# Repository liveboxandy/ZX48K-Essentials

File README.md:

# ZX Spectrum 48K Essentials

This clone of the original (https://github.com/tomekszafranski/ZX48K-Essentials) has the following additions,

Full KiCAD 10 project including Schematic, PCB Data, Footprints, 3D Models and Symbols. 

No changes were made to the pcb layout or traces.

Symbols were adjusted to follow the original pdf schematic.
Footprints were adjusted to fit the original pcb layout. 
Vias were a best guess for sizes.
The BOM has not changed other than the JST connector should be JST_SHL_SM08B-SHLS-TF_1x08-1MP type.

Original README.md follows,

## Introduction

Sinclair ZX Spectrum 48K computer released in April 1982 was not the best one compared to its competitors but for sure became one of the most influential ones. A lot of hobbyists who nowadays collect, repair or mod Spectrum, might be tempted to create their own version - keeping the original idea/design that makes a Z80 system the Spectrum: ULA with its contended memory architecture, content of the ROM, original case and rubber keyboard but getting rid of all nonsenses where you could easily do better, even back then. 

It has to be said that this is not by any means revolutionary work. There are lots of similar projects and this one could easily be called Another Spectrum Clone but as mentioned before, every Spectrum lover would like to have his/her own version. I hope you like mine.

## Design

The idea is to leave all ZX Spectrum 48K components as they were and introduce only minimal changes. 

The main design decision concerns ULA. You might want to use original chip but it is difficult to get and you need to clone extensive analog video circuit (that occupies one third of the board) still getting relatively poor composite picture. On the other hand, you could use modern FPGA replacement that has RGB output - but this would not be ULA architecture (on the outside) any longer. I decided to use [vLA82S+](https://www.vretrodesign.com/products/vla82s-spectrum-ula-replacement-with-rgb-interface-and-ay-emulator-without-interface) by vRetro Design which is FPGA based ULA with RGB output but also a drop-in replacement for original chip so Sinclair's architecture will be preserved. Other changes are:

* Dynamically refreshed Lower RAM based on 4116 chips is replaced with more convenient static RAM which also allows to get rid of almost all of power supply section as -5V and +12V voltages are no longer needed. This is the solution commonly used in modern [memory replacements modules](https://www.retroleum.co.uk/spectrum-repairs-mods) – using set of flip-flops (74LS574) to hook up single RAM chip to raw/column address multiplexers used in original design.

* Dynamically refreshed Upper RAM 4132/64 chips use only one voltage, however they could easily be replaced with one 32KB static RAM chip. Memory type selection jumpers are no longer needed.
  
* While building your ZX Spectrum you probably will not source (difficult to get) original PROM but instead use modern EEPROM like W27C512 that you program with [content of the ROM](https://speccy4ever.speccy.org/_SIN.htm). ROM type jumpers are no longer needed.
  
* In power supply section efficient modern switching regulator is used that doesn't require a radiator. Also (as in MAX/Harlequin) bridge rectifier is added to save from mistakenly connecting power supply with wrong polarity (which from experience is likely to happen if you use more machines because Spectrum uses center-negative power jack while nowadays almost everything is center-positive).

Everything else is left intact.

## Parts

* Except for added components (marked with numbers 200+) all others <ins>have original references and are located in the same places</ins> on a PCB as in ZX Spectrum 48K Issue 3B. Four unmarked small elements are additional decoupling 100nF capacitors (P=2.5mm) for added ICs.
  
* Standard size 0,25W resistors are used, however compared to original their length is decreased from 0.6” to 0,5”. I really hate those banks of bus separation/pullup resistors so network ones are used wherever possible.
  
* Axial capacitors are used as in original design but you can install disc ones instead. I could not resist and left blue electrolytic capacitors (only two since there are no power and video sections), however there are mounting holes underneath (P=2.0mm) to use radial ones as well. 
  
* Original audio sockets are replaced with PJ-307 ones, commonly used in retro systems nowadays.
  
* Mini DIN8 connector (as in Harlequin 48K) is used to output RGB signal and mono sound to TV/monitor using [RGB Scart Lead cable](https://www.ebay.com/itm/253830448917?epid=17023035733&itmmeta=01JKTFD61QHFB48BB7ZDRB7SRS&hash=item3b19794715:g:KvwAAOSwlb5nn9B-).
  
* If you think using bridge rectifier is below you, shorten its pins: 1-4, 2-3 and don’t use it.

* Be aware that 40 ohm speaker might be difficult to find.

## Board

Here is KiCad project of the board.

Fully assembled ZX48essentials PCB, tested with [Diagnostic ROM](https://blog.retroleum.co.uk/electronics-articles/a-diagnostic-rom-image-for-the-zx-spectrum/), Kempston Pro Joystick Interface, [divMMC Future](https://www.tfw8b.com/product/divmmc-future-sinclair-zx-spectrum/), [ZX Interface 2](https://en.wikipedia.org/wiki/ZX_Interface_2) and [MaxDuino](https://lotharek.pl/productdetail.php?id=409).

## Remarks

* Because power section is severely reduced, only +5V is available on edge connector. Also no video signals are present.
  
* If you intend to put the board in ZX Spectrum 48K case, vLA82S+ must be soldered. For ZX Spectrum 48K+ case you can use socket (standard not precision).

* Geoff Wearmouth's [Looking Glass ROM](https://drive.google.com/file/d/1Mf0jTW43AdGkd5ZbCQTpsrJHTxZ-JjuA/view) is worth checking.
  
* As a bonus, vLA82S+ has write-only AY-3-8910 compatible sound generator built-in. L and R channels are mixed and output as one to TV/monitor through mini DIN socket. If you connect microSD card interface that often has joystick port, you have everything you need :-)

Have fun!

Tomek

> [!NOTE]
> **Disclaimer**: This is my project that I’ve built and it works for me. You can do it as well but remember, you’re responsible for your own doings and the consequences, not me.
>
> **Licensed under**: CERN Open Hardware Licence Version 2 - Strongly Reciprocal. Read [CERN-OHL-S](https://ohwr.org/cern_ohl_s_v2.txt)

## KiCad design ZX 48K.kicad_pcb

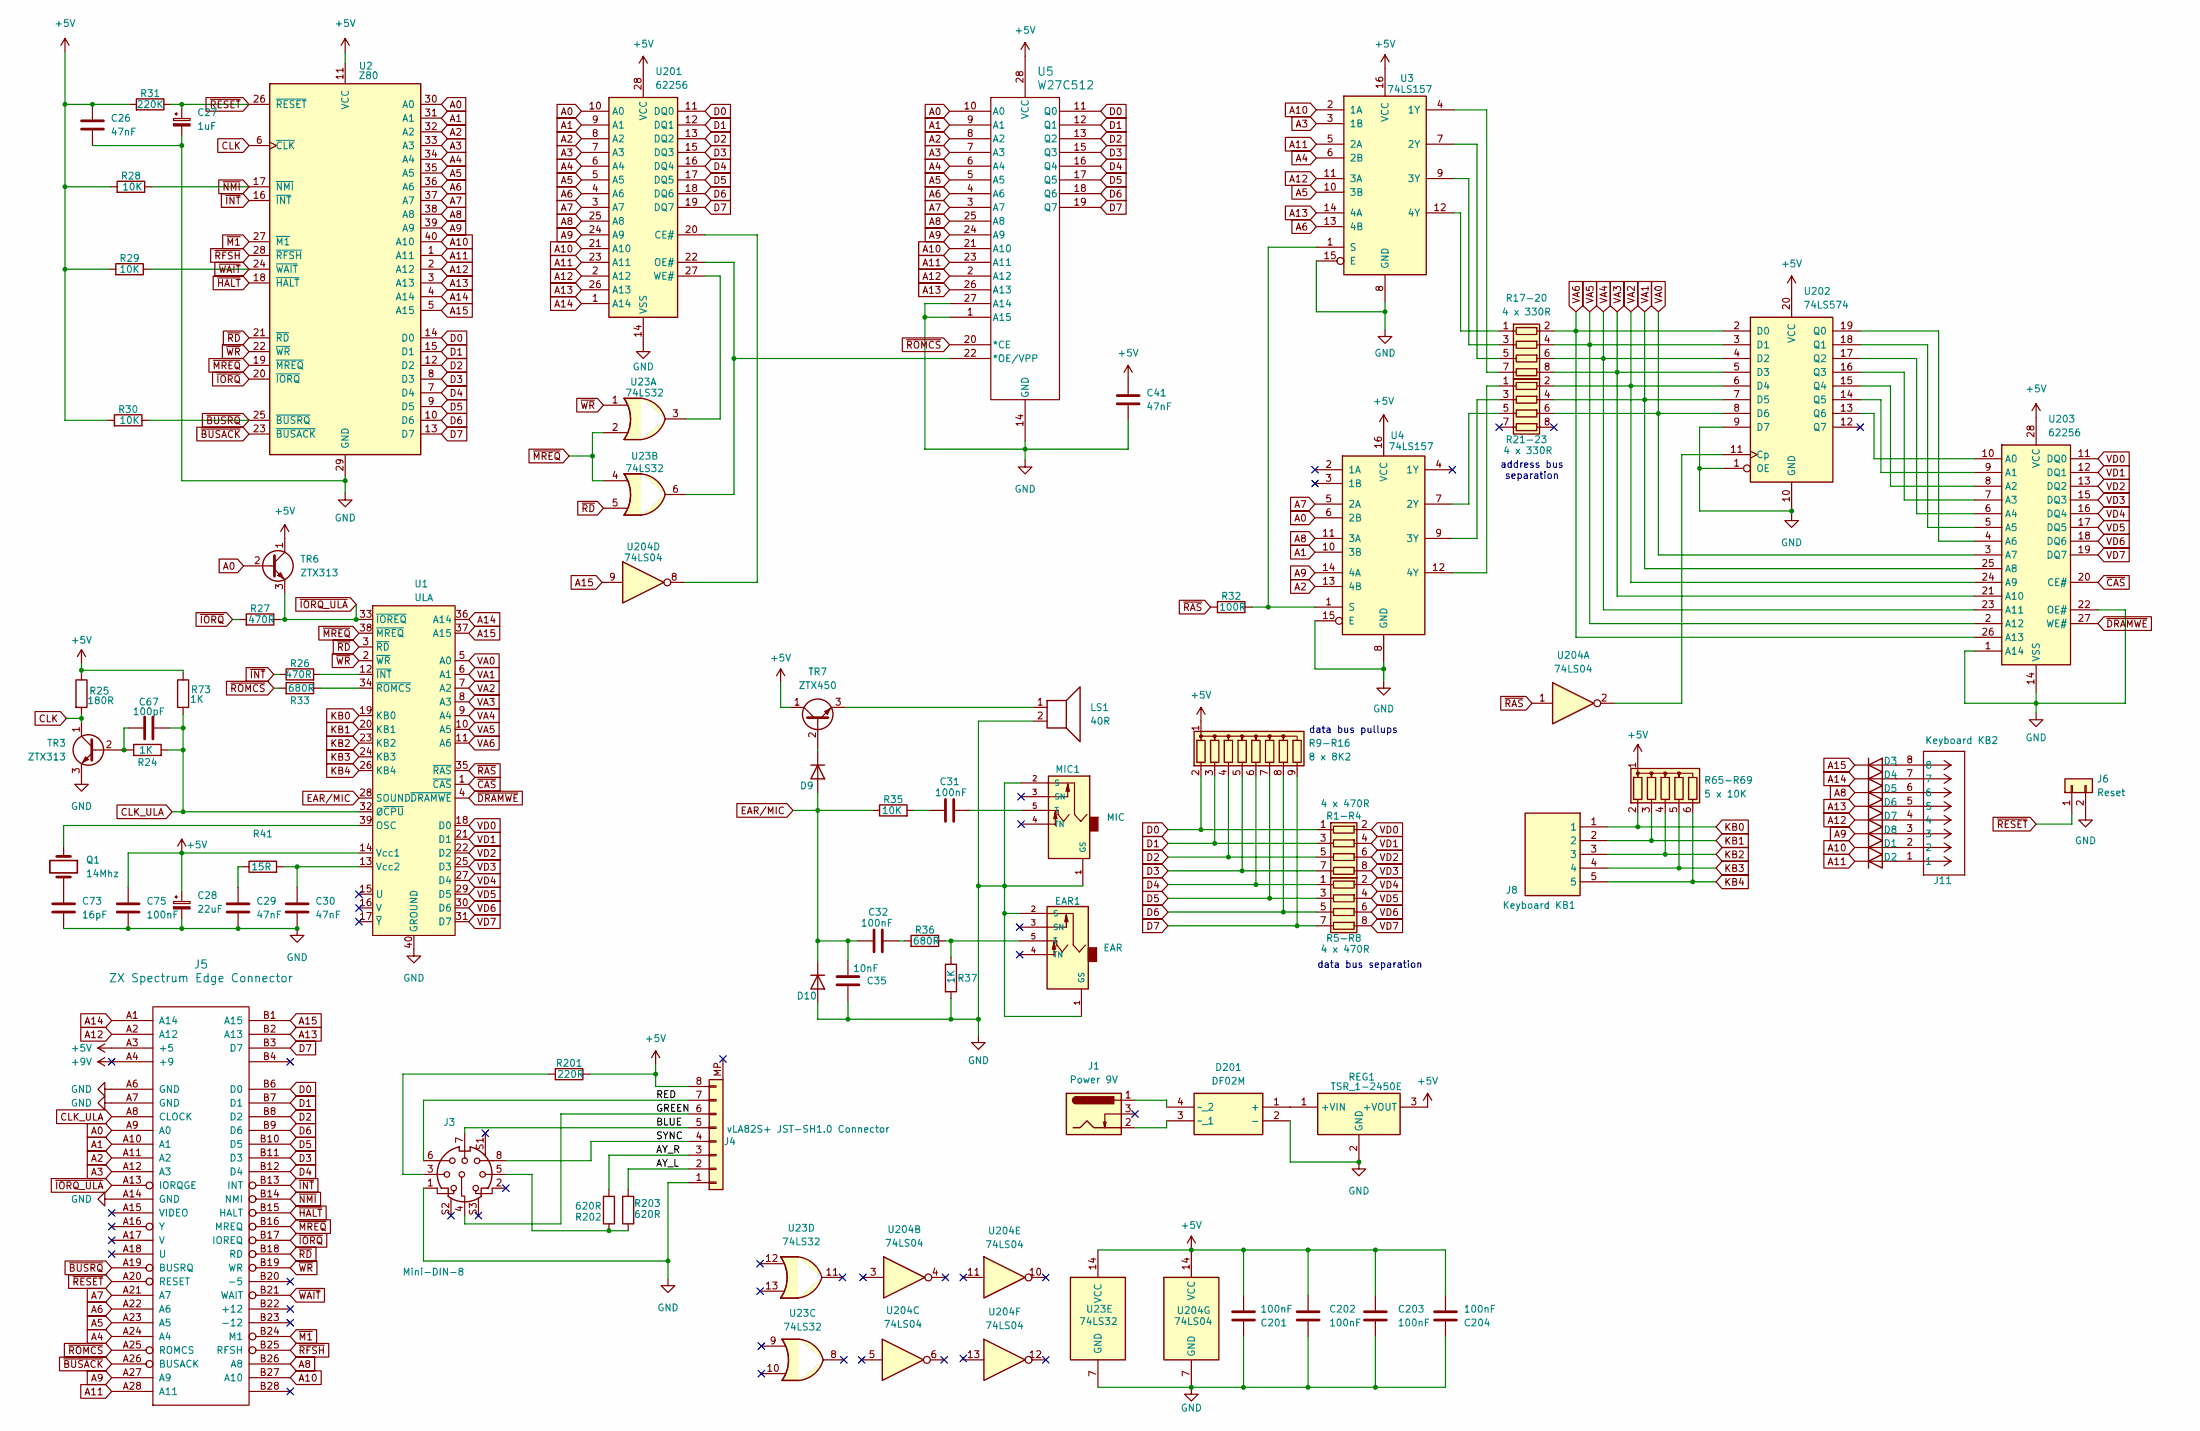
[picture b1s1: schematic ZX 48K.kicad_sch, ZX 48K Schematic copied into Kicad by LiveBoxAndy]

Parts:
C26, C29, C30, C41: 47nF; C_Axial_L7.8mm_D2.4mm_P12.7mm_Horizontal
C27: 1uF; CP_Axial_L15.6mm_D6.0mm_P20.00mm_Horizontal
C28: 22uF; CP_Axial_L15.6mm_D6.0mm_P20.00mm_Horizontal
C31, C32, C75: 100nF; C_Axial_L7.8mm_D2.4mm_P12.7mm_Horizontal
C35: 10nF; C_Axial_L7.8mm_D2.4mm_P12.7mm_Horizontal
C67: 100pF; C_Axial_L7.8mm_D2.4mm_P12.7mm_Horizontal
C73: 16pF; C_Axial_L7.8mm_D2.4mm_P12.7mm_Horizontal
C201, C202, C203, C204: 100nF; C_Disc_D3.0mm_W1.6mm_P2.50mm
D1, D2, D3, D4, D5, D6, D7, D8, D9, D10: 1N4148; D_DO-35_SOD27_P12.70mm_Horizontal
D201: DF02M
EAR1: EAR; PJ-307
J1: Power 9V; BarrelJack_Horizontal
J3: Mini-DIN-8; KYCON_KMDGX-8S-AS
J4: vLA82S+ JST-SH1.0 Connector; JST_SHL_SM08B-SHLS-TF_1x08-1MP_P1.00mm_Horizontal
J5: ZX Spectrum Edge Connector; ZX_BUS_B_TOP
J6: Reset; SAMTEC_TSW-102-07-G-S
J8: Keyboard KB1; Keyboard5x1
J11: Keyboard KB2; Keyboard8x1
LS1: 40R; Speaker
MIC1: MIC; PJ-307
Q1: 14Mhz; X1
R1-R4, R5-R8: 4 x 470R; 4308R102203LF
R9-R16: 8 x 8K2; R_Array_SIP9
R17-20, R21-23: 4 x 330R; 4308R102203LF
R24, R37, R73: 1K; R_Axial_L7.8mm_D2.4mm_P12.7mm_Horizontal
R25: 180R; R_Axial_L7.8mm_D2.4mm_P12.7mm_Horizontal
R26, R27: 470R; R_Axial_L7.8mm_D2.4mm_P12.7mm_Horizontal
R28, R29, R30, R35: 10K; R_Axial_L7.8mm_D2.4mm_P12.7mm_Horizontal
R31: 220K; R_Axial_L7.8mm_D2.4mm_P12.7mm_Horizontal
R32: 100R; R_Axial_L7.8mm_D2.4mm_P12.7mm_Horizontal
R33, R36: 680R; R_Axial_L7.8mm_D2.4mm_P12.7mm_Horizontal
R41: 15R; R_Axial_DIN0414_L11.9mm_D4.5mm_P20.32mm_Horizontal
R65-R69: 5 x 10K; R_Array_SIP6
R201: 220R; R_Axial_L7.8mm_D2.4mm_P12.7mm_Horizontal
R202, R203: 620R; R_Axial_L7.8mm_D2.4mm_P12.7mm_Horizontal
REG1: TSR_1-2450E; TSR12450E
TR3, TR6: ZTX313; TO-92Flat
TR7: ZTX450; TO-92Flat
U1: ULA; DIP-40_W15.24mm_Socket
U2: Z80; DIP-40_W15.24mm_Socket
U3, U4: 74LS157; DIP-16_W7.62mm_Socket
U5: W27C512; DIP-28_W15.24mm_Socket
U23: 74LS32; DIP-14_W7.62mm_Socket
U201, U203: 62256; DIP-28_W15.24mm_Socket
U202: 74LS574; DIP-20_W7.62mm_Socket
U204: 74LS04; DIP-14_W7.62mm_Socket

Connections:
+5V: C26.1, C28.1, C41.1, C75.1, C201.2, C202.1, C203.1, C204.2, J4.8, J5.A3 (+5), R9-R16.1 (common), R25.1, R28.2, R29.2, R30.2, R31.2, R65-R69.1 (common), R73.1, R201.1, REG1.3 (+VOUT), TR6.1 (C), TR7.1 (C), U1.14 (Vcc1), U2.11 (VCC), U3.16 (VCC), U4.16 (VCC), U5.28 (VCC), U23.14 (VCC), U201.28 (VCC), U202.20 (VCC), U203.28 (VCC), U204.14 (VCC)
+9V: J5.A4 (+9)
/AY_L: J4.2, R203.2
/AY_R: J4.3, R202.2
/BLUE: J3.7, J4.5
/GREEN: J3.4, J4.6
/RED: J3.6, J4.7
/SYNC: J3.8, J4.4
A0: J5.A9 (A0), TR6.2 (B), U2.30 (A0), U4.6 (2B), U5.10 (A0), U201.10 (A0)
A1: J5.A10 (A1), U2.31 (A1), U4.10 (3B), U5.9 (A1), U201.9 (A1)
A2: J5.A11 (A2), U2.32 (A2), U4.13 (4B), U5.8 (A2), U201.8 (A2)
A3: J5.A12 (A3), U2.33 (A3), U3.3 (1B), U5.7 (A3), U201.7 (A3)
A4: J5.A24 (A4), U2.34 (A4), U3.6 (2B), U5.6 (A4), U201.6 (A4)
A5: J5.A23 (A5), U2.35 (A5), U3.10 (3B), U5.5 (A5), U201.5 (A5)
A6: J5.A22 (A6), U2.36 (A6), U3.13 (4B), U5.4 (A6), U201.4 (A6)
A7: J5.A21 (A7), U2.37 (A7), U4.5 (2A), U5.3 (A7), U201.3 (A7)
A8: D5.1 (K), J5.B26 (A8), U2.38 (A8), U4.11 (3A), U5.25 (A8), U201.25 (A8)
A9: D8.1 (K), J5.A27 (A9), U2.39 (A9), U4.14 (4A), U5.24 (A9), U201.24 (A9)
A10: D1.1 (K), J5.B27 (A10), U2.40 (A10), U3.2 (1A), U5.21 (A10), U201.21 (A10)
A11: D2.1 (K), J5.A28 (A11), U2.1 (A11), U3.5 (2A), U5.23 (A11), U201.23 (A11)
A12: D7.1 (K), J5.A2 (A12), U2.2 (A12), U3.11 (3A), U5.2 (A12), U201.2 (A12)
A13: D6.1 (K), J5.B2 (A13), U2.3 (A13), U3.14 (4A), U5.26 (A13), U201.26 (A13)
A14: D4.1 (K), J5.A1 (A14), U1.36 (A14), U2.4 (A14), U201.1 (A14)
A15: D3.1 (K), J5.B1 (A15), U1.37 (A15), U2.5 (A15), U204.9
CLK: R25.2, TR3.1 (C), U2.6 (~CLK)
CLK_ULA: C67.2, J5.A8 (CLOCK), R24.2, R73.2, U1.32 (Ø~CPU)
D0: J5.B6 (D0), R1-R4.1 (R1.1), R9-R16.2 (R1), U2.14 (D0), U5.11 (Q0), U201.11 (DQ0)
D1: J5.B7 (D1), R1-R4.3 (R2.1), R9-R16.3 (R2), U2.15 (D1), U5.12 (Q1), U201.12 (DQ1)
D2: J5.B8 (D2), R1-R4.5 (R3.1), R9-R16.4 (R3), U2.12 (D2), U5.13 (Q2), U201.13 (DQ2)
D3: J5.B11 (D3), R1-R4.7 (R4.1), R9-R16.5 (R4), U2.8 (D3), U5.15 (Q3), U201.15 (DQ3)
D4: J5.B12 (D4), R5-R8.1 (R1.1), R9-R16.6 (R5), U2.7 (D4), U5.16 (Q4), U201.16 (DQ4)
D5: J5.B10 (D5), R5-R8.3 (R2.1), R9-R16.7 (R6), U2.9 (D5), U5.17 (Q5), U201.17 (DQ5)
D6: J5.B9 (D6), R5-R8.5 (R3.1), R9-R16.8 (R7), U2.10 (D6), U5.18 (Q6), U201.18 (DQ6)
D7: J5.B3 (D7), R5-R8.7 (R4.1), R9-R16.9 (R8), U2.13 (D7), U5.19 (Q7), U201.19 (DQ7)
EAR/MIC: C32.1, C35.1, D9.2 (A), D10.1 (K), R35.1, U1.28 (SOUND)
GND: C26.2, C27.2, C28.2, C29.2, C30.2, C35.2, C41.2, C73.2, C75.2, C201.1, C202.2, C203.2, C204.1, D10.2 (A), D201.2 (-), EAR1.1 (GS), EAR1.2 (S), J3.1, J4.1, J5.A6 (GND), J5.A7 (GND), J5.A14 (GND), J6.2, LS1.2, MIC1.1 (GS), MIC1.2 (S), R37.2, REG1.2 (GND), TR3.3 (E), U1.40 (GROUND), U2.29 (GND), U3.8 (GND), U3.15 (E), U4.8 (GND), U4.15 (E), U5.1 (A15), U5.14 (GND), U5.27 (A14), U23.7 (GND), U201.14 (VSS), U202.1 (OE), U202.9 (D7), U202.10 (GND), U203.1 (A14), U203.14 (VSS), U203.22 (OE#), U204.7 (GND)
KB0: J8.1, R65-R69.2 (R1), U1.19 (KB0)
KB1: J8.2, R65-R69.3 (R2), U1.20 (KB1)
KB2: J8.3, R65-R69.4 (R3), U1.23 (KB2)
KB3: J8.4, R65-R69.5 (R4), U1.24 (KB3)
KB4: J8.5, R65-R69.6 (R5), U1.26 (KB4)
unnamed: C29.1, R41.1
unnamed: C31.2, R35.2
unnamed: C32.2, R36.2
unnamed: C73.1, Q1.2
unnamed: D1.2 (A), J11.2
unnamed: D2.2 (A), J11.1
unnamed: D3.2 (A), J11.8
unnamed: D4.2 (A), J11.7
unnamed: D5.2 (A), J11.6
unnamed: D6.2 (A), J11.5
unnamed: D7.2 (A), J11.4
unnamed: D8.2 (A), J11.3
unnamed: D9.1 (K), TR7.2 (B)
unnamed: D201.1 (+), REG1.1 (+VIN)
unnamed: D201.3 (~_1), J1.2
unnamed: D201.4 (~_2), J1.1
unnamed: EAR1.5 (T), R36.1, R37.1
unnamed: J3.3, R201.2
unnamed: J3.5, R202.1, R203.1
unnamed: C31.1, MIC1.5 (T)
unnamed: R17-20.1 (R1.1), U3.12 (4Y)
unnamed: R17-20.3 (R2.1), U3.9 (3Y)
unnamed: R17-20.5 (R3.1), U3.7 (2Y)
unnamed: R17-20.7 (R4.1), U3.4 (1Y)
unnamed: R21-23.1 (R1.1), U4.12 (4Y)
unnamed: R21-23.3 (R2.1), U4.9 (3Y)
unnamed: R21-23.5 (R3.1), U4.7 (2Y)
unnamed: C67.1, R24.1, TR3.2 (B)
unnamed: LS1.1, TR7.3 (E)
unnamed: Q1.1, U1.39 (OSC)
unnamed: C30.1, R41.2, U1.13 (Vcc2)
unnamed: R26.2, U1.12 (~INT)
unnamed: R33.1, U1.34 (~ROMCS)
unnamed: R32.1, U3.1 (S), U4.1 (S)
unnamed: U201.20 (CE#), U204.8
unnamed: U5.22 (*OE/VPP), U23.6, U201.22 (OE#)
unnamed: U23.3, U201.27 (WE#)
unnamed: U202.11 (Cp), U204.2
unnamed: U202.19 (Q0), U203.4 (A6)
unnamed: U202.18 (Q1), U203.5 (A5)
unnamed: U202.17 (Q2), U203.6 (A4)
unnamed: U202.16 (Q3), U203.7 (A3)
unnamed: U202.15 (Q4), U203.8 (A2)
unnamed: U202.14 (Q5), U203.9 (A1)
unnamed: U202.13 (Q6), U203.10 (A0)
VA0: R21-23.6 (R3.2), U1.5 (A0), U202.8 (D6), U203.3 (A7)
VA1: R21-23.4 (R2.2), U1.6 (A1), U202.7 (D5), U203.25 (A8)
VA2: R21-23.2 (R1.2), U1.7 (A2), U202.6 (D4), U203.24 (A9)
VA3: R17-20.8 (R4.2), U1.8 (A3), U202.5 (D3), U203.21 (A10)
VA4: R17-20.6 (R3.2), U1.9 (A4), U202.4 (D2), U203.23 (A11)
VA5: R17-20.4 (R2.2), U1.10 (A5), U202.3 (D1), U203.2 (A12)
VA6: R17-20.2 (R1.2), U1.11 (A6), U202.2 (D0), U203.26 (A13)
VD0: R1-R4.2 (R1.2), U1.18 (D0), U203.11 (DQ0)
VD1: R1-R4.4 (R2.2), U1.21 (D1), U203.12 (DQ1)
VD2: R1-R4.6 (R3.2), U1.22 (D2), U203.13 (DQ2)
VD3: R1-R4.8 (R4.2), U1.25 (D3), U203.15 (DQ3)
VD4: R5-R8.2 (R1.2), U1.27 (D4), U203.16 (DQ4)
VD5: R5-R8.4 (R2.2), U1.29 (D5), U203.17 (DQ5)
VD6: R5-R8.6 (R3.2), U1.30 (D6), U203.18 (DQ6)
VD7: R5-R8.8 (R4.2), U1.31 (D7), U203.19 (DQ7)
~BUSACK: J5.A26 (BUSACK), U2.23 (~BUSACK)
~BUSRQ: J5.A19 (BUSRQ), R30.1, U2.25 (~BUSRQ)
~CAS: U1.1 (~CAS), U203.20 (CE#)
~DRAMWE: U1.4 (~DRAMWE), U203.27 (WE#)
~HALT: J5.B15 (HALT), U2.18 (~HALT)
~INT: J5.B13 (INT), R26.1, U2.16 (~INT)
~IORQ_ULA: J5.A13 (IORQGE), R27.1, TR6.3 (E), U1.33 (~IOREQ)
~IORQ: J5.B17 (IOREQ), R27.2, U2.20 (~IORQ)
~M1: J5.B24 (M1), U2.27 (~M1)
~MREQ: J5.B16 (MREQ), U1.38 (~MREQ), U2.19 (~MREQ), U23.2, U23.4
~NMI: J5.B14 (NMI), R28.1, U2.17 (~NMI)
~RAS: R32.2, U1.35 (~RAS), U204.1
~RD: J5.B18 (RD), U1.3 (~RD), U2.21 (~RD), U23.5
~RESET: C27.1, J5.A20 (RESET), J6.1, R31.1, U2.26 (~RESET)
~RFSH: J5.B25 (RFSH), U2.28 (~RFSH)
~ROMCS: J5.A25 (ROMCS), R33.2, U5.20 (*CE)
~WAIT: J5.B21 (WAIT), R29.1, U2.24 (~WAIT)
~WR: J5.B19 (WR), U1.2 (~WR), U2.22 (~WR), U23.1

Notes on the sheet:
address bus separation
data bus separation
data bus pullups

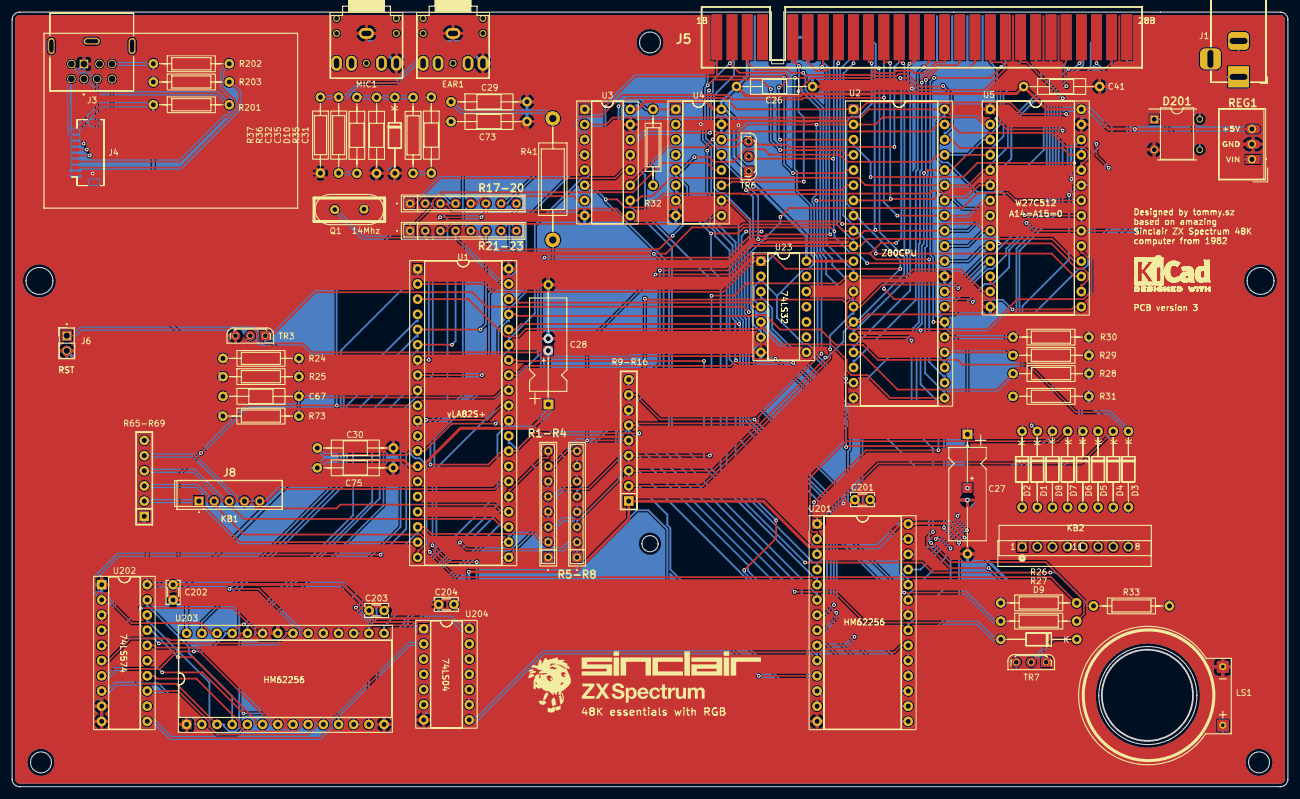
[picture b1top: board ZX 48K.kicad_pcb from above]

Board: 2 copper layers, 213.1 x 129.3 mm, 76 parts (0 on the bottom side), 118 nets.
